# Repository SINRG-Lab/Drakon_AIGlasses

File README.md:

# Drakon AI Glasses

Hardware, firmware, 3D models, and the companion iOS app for Drakon AI smart glasses.

This repository is the single home for everything physical and embedded: board
designs, embedded firmware, printable frame parts, and the companion iOS app.
Measurement studies and backend services live in other repositories.

## Editions

The glasses come in two open-source editions that share a frame and audio
pipeline but differ in how they reach the network.

| Edition | Directory | Connectivity | Status |
|---|---|---|---|
| Companion | [`companion/`](companion/) | Wi-Fi / BLE, relayed via a paired device | v3 fabricated, v4 in design |
| Standalone | [`standalone/`](standalone/) | On-board cellular | v1 in design |

## Versions

Each edition is numbered independently — `companion/v3` and `standalone/v1` are
unrelated designs. Numbering continues each edition's own history, so the
companion boards start at v3 to match the `pcbv3` the team already builds.

| Version | Status |
|---|---|
| [`companion/v3`](companion/v3/) | **Current** — left and right boards fabricated |
| [`companion/v4`](companion/v4/) | Next — in design, empty |
| [`standalone/v1`](standalone/v1/) | First board — in design, empty |

A new version directory is created when the PCB changes in a way that breaks
compatibility with existing firmware or frame parts. Small fixes land in the
existing version. See [`docs/versioning.md`](docs/versioning.md).

## Layout

Every build is **two PCBs**, one per temple, so `hardware/` splits left/right.

```
<edition>/<version>/
├── firmware/            Embedded source for that board version
│   ├── src/  include/  lib/
├── hardware/
│   ├── left/            Left temple board
│   │   ├── kicad/       The KiCad project — .kicad_pro, .kicad_sch, .kicad_pcb
│   │   ├── fabrication/ gerbers/ and position/ files as sent to the fab
│   │   ├── bom/         Bills of materials
│   │   └── exports/     Schematic PDFs, STEP models, renders
│   ├── right/           Right temple board — same layout
│   └── shared/          Symbols, footprints and datasheets used by both
└── 3d-models/
    ├── cad/             Editable CAD source (STEP, SLDPRT, F3D)
    ├── exports/         Print-ready meshes (STL, 3MF)
    └── renders/         Images for docs and papers

common/                  Shared across editions and versions
├── firmware/  hardware/  3d-models/  scripts/

docs/
├── specs/  assembly/  bring-up/  versioning.md
```

The companion edition also contains the XIAO development firmware at
[`companion/firmware/S3_App_V2/`](companion/firmware/S3_App_V2/) and the iOS
app at [`companion/ios/`](companion/ios/). These came from the MK3.5 development
work; the firmware targets **XIAO ESP32-S3 Sense**, with its own pin map. It is
not a firmware release for the ESP32-C6 v3 boards. See the
[companion setup instructions](companion/README.md#software).

## Conventions

- **Keep each KiCad project in one directory.** `.kicad_pro`, `.kicad_sch` and
  `.kicad_pcb` must sit together under `kicad/` or the project will not open.
- **Put a file under `common/` only once a second edition or version actually
  uses it.** Premature sharing is harder to undo than duplication.
- **Commit CAD source alongside exports.** An STL with no editable source is a
  dead end.
- **Commit fabrication outputs even though they are generated.** They are the
  exact files sent to the fab; regenerating from a newer KiCad will not
  reproduce what was actually built.
- **Never commit secrets.** Firmware credentials belong in an ignored
  `config.h` beside a committed `config.h.template`.
- **Do not commit KiCad backups, `fp-info-cache`, or `.kicad_prl`.** They are
  local caches and editor state; `.gitignore` covers them.

## Git LFS

CAD, mesh, fabrication and datasheet binaries are tracked with
[Git LFS](https://git-lfs.com) — see [`.gitattributes`](.gitattributes). Run
this once per clone, before adding any such files:

```
git lfs install
```

Note that binaries committed before LFS was configured remain ordinary blobs in
history. Converting them requires `git lfs migrate`, which rewrites history and
needs a force-push — coordinate with the team before doing it.

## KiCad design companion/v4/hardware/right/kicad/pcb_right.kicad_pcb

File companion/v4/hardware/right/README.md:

# Companion v3 — Right Hinge Board

KiCad project `pcb_right`. Board outline **40.0 × 20.2 mm**, 16 components —
a smaller board than the left, with no battery.

| Directory | Contents |
|---|---|
| `kicad/` | `pcb_right.kicad_pro`, `.kicad_sch`, `.kicad_pcb`, library tables |
| `fabrication/position/` | `CPL_V4_RIGHT.csv`, `pcb_right-top.CSV` |
| `bom/` | `BOM_V4_RIGHT.csv`, `pcb_right.csv` |
| `exports/` | `pcb_right.step` |

Symbols and footprints are in [`../shared/symbols/`](../shared/symbols/),
shared with the left board.

## ⚠ No gerbers exist for this board

The original upload had a folder called `pcbv3_right_frabrication_files`, but
its `gerber/` subfolder did **not** contain this board. Those files were a
second export of the *left* board, and have been moved to
[`../left/fabrication/gerbers-2026-06-04/`](../left/fabrication/gerbers-2026-06-04/).

Three independent checks agree:

| Check | Left board | Right board | The misfiled gerbers |
|---|---|---|---|
| Edge cuts outline | 58.64 × 12.9 mm | 40.0 × 20.2 mm | 58.64 × 12.9 mm |
| Drill-pattern match | — | 2.1% | 70.8% to the left board |
| `%TF.ProjectId` | `pcbvr_left` | — | `pcbvr_left` |

**Anyone who sent that folder to a fab would have received a second left
board.** Export gerbers from `kicad/pcb_right.kicad_pcb` before ordering.

The BOM and position files in this directory *are* genuinely this board — their
designators (`C1`–`C4`, `FB1`, `FB2`, `J1`, `J2`, `R1`–`R3`, `SW1`, `U1`, `U2`)
all fall within its 16 components and include none of the left board's
battery, diodes or extra passives. Only the gerbers were misfiled.

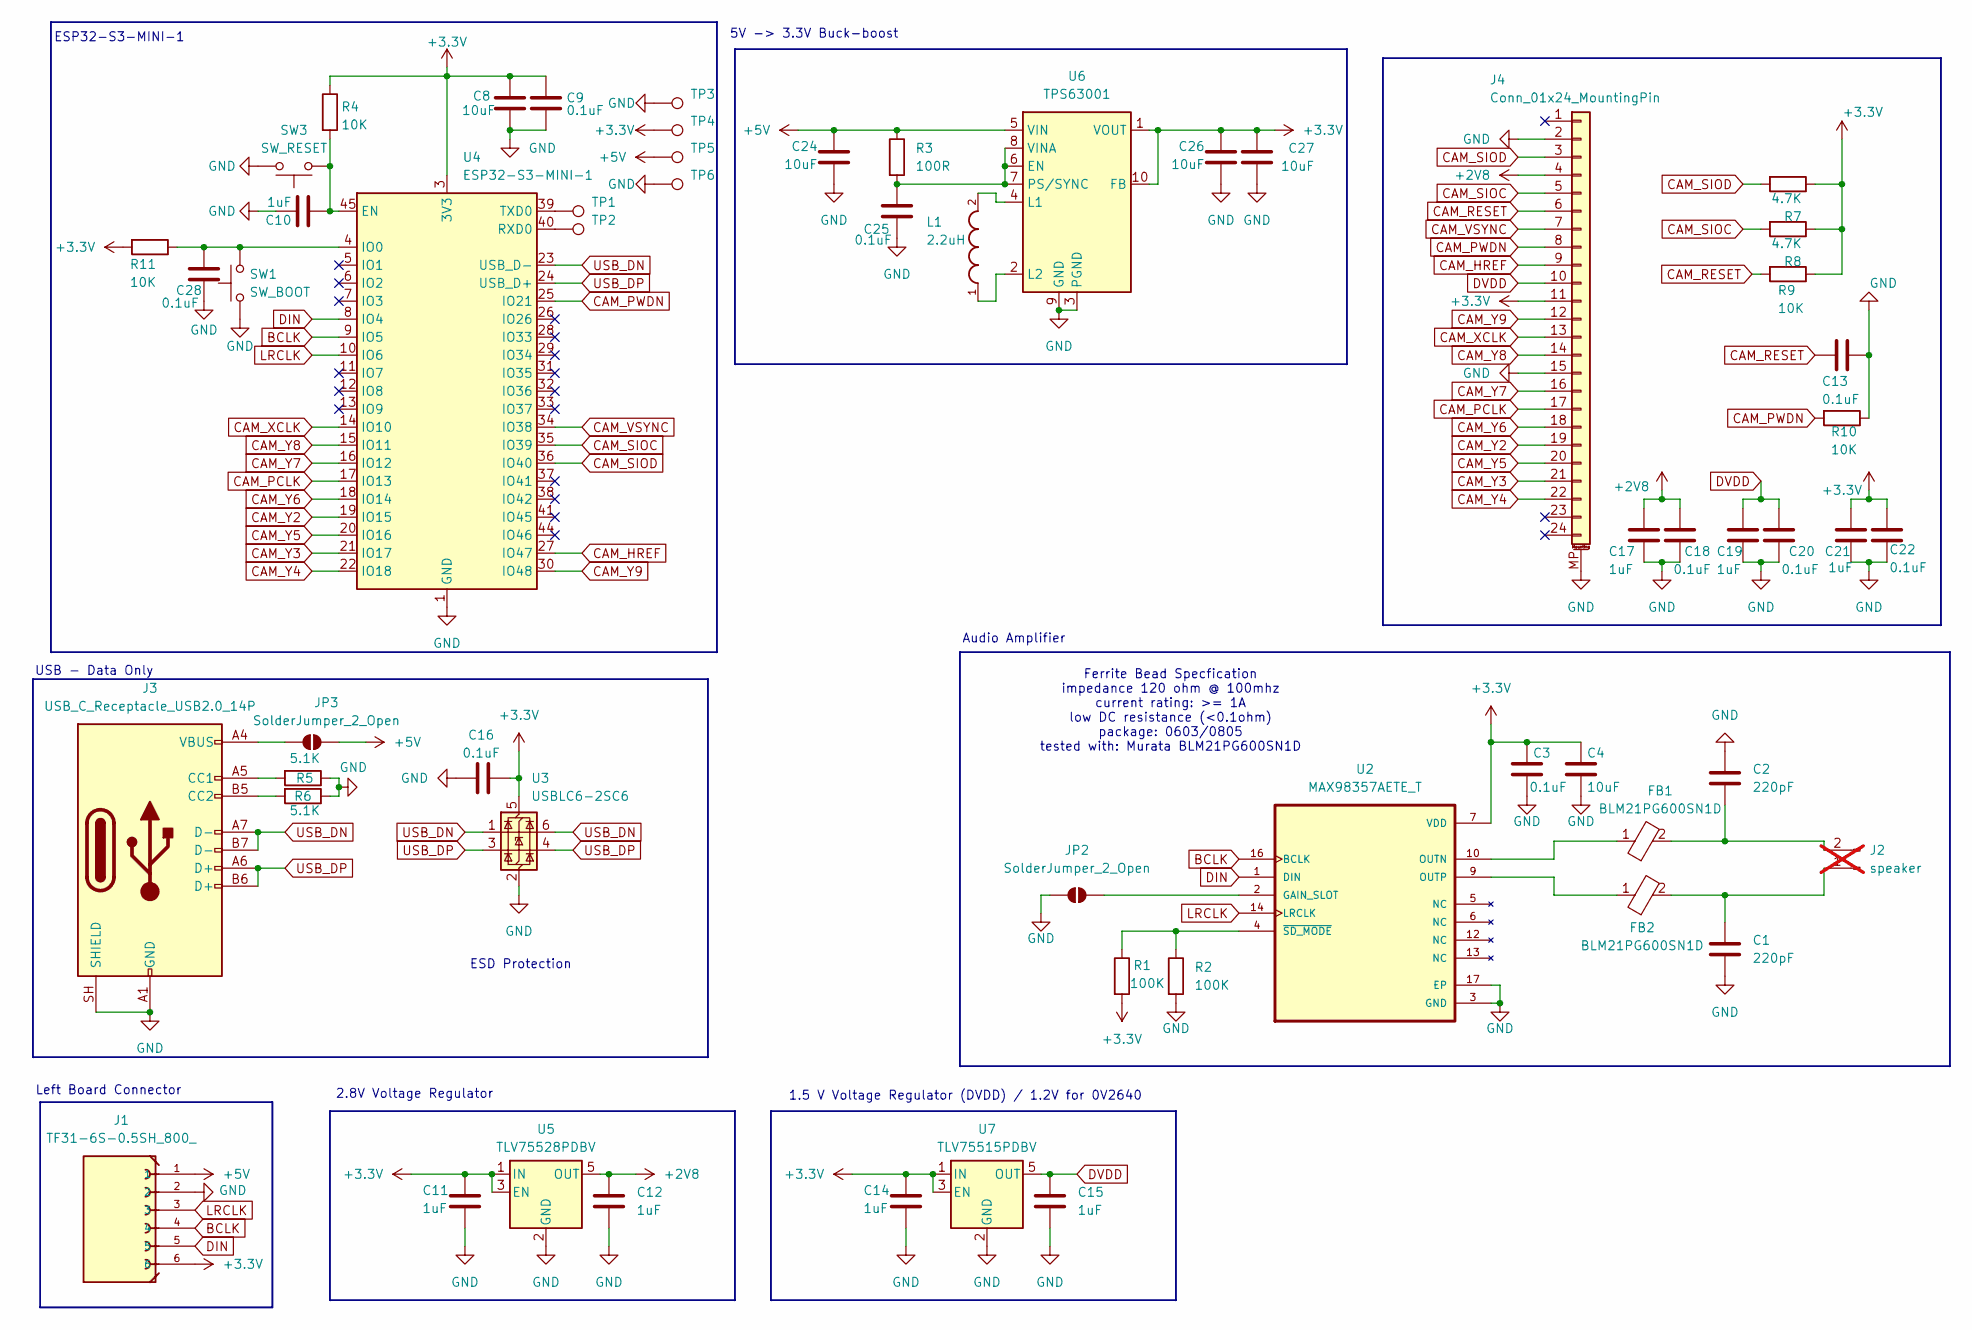
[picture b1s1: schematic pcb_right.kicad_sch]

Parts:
C1, C2: 220pF; C_0805_2012Metric_Pad1.18x1.45mm_HandSolder; Manufacturer_Part_Number CC0805KRX7R9BB221; JLCPCB_Part# C107145
C3: 0.1uF; C_0805_2012Metric_Pad1.18x1.45mm_HandSolder; Manufacturer_Part_Number CC0805KRX7R9BB104; JLCPCB_Part# C49678
C4: 10uF; C_0805_2012Metric_Pad1.18x1.45mm_HandSolder; Manufacturer_Part_Number CL21A106KAYNNNE; JLCPCB_Part# C15850
C8, C24, C26, C27: 10uF; C_0402_1005Metric; Manufacturer_Part_Number CL05A106MP5NUNC; JLCPCB_Part# C315248
C9, C13, C16, C18, C20, C22, C25, C28: 0.1uF; C_0402_1005Metric; Manufacturer_Part_Number CL05B104KO5NNNC; JLCPCB_Part# C1525
C10, C11, C12, C14, C15, C17, C19, C21: 1uF; C_0402_1005Metric; Manufacturer_Part_Number CL05A105KA5NQNC; JLCPCB_Part# C52923
FB1, FB2: BLM21PG600SN1D; BLM21AG102BH1J; Mouser Part Number 81-BLM21P600S
J1: TF31-6S-0.5SH_800_; HRS_TF31-6S-0.5SH_800_; Manufacturer_Part_Number TF31-6S-0.5SH(800); JLCPCB_Part# C3195341
J2: speaker; PinHeader_1x02_P2.54mm_Vertical; not fitted
J3: USB_C_Receptacle_USB2.0_14P; USB_C_Receptacle_HRO_TYPE-C-31-M-12; Manufacturer_Part_Number TYPE-C-31-M-12; JLCPCB_Part# C165948
J4: Conn_01x24_MountingPin; Hirose_FH12-24S-0.5SH_1x24-1MP_P0.50mm_Horizontal; Manufacturer_Part_Number FH12-24S-0.5SH(55); JLCPCB_Part# C202112
JP2, JP3: SolderJumper_2_Open; SolderJumper-2_P1.3mm_Open_RoundedPad1.0x1.5mm
L1: 2.2uH; INDC2520X120N; Manufacturer_Part_Number DFE252012F-2R2M=P2; JLCPCB_Part# C576403
R1, R2: 100K; R_0805_2012Metric_Pad1.20x1.40mm_HandSolder; Manufacturer_Part_Number 0805W8F1003T5E; JLCPCB_Part# C149504
R3: 100R; R_0805_2012Metric_Pad1.20x1.40mm_HandSolder; Manufacturer_Part_Number 0805W8F1000T5E; JLCPCB_Part# C17408
R4, R11: 10K; R_0402_1005Metric; Manufacturer_Part_Number 0402WGF1002TCE; JLCPCB_Part# C25744
R5, R6: 5.1K; R_0402_1005Metric; Manufacturer_Part_Number 0402WGF5101TCE; JLCPCB_Part# C25905
R7, R8: 4.7K; R_0805_2012Metric_Pad1.20x1.40mm_HandSolder; Manufacturer_Part_Number 0805W8F4701T5E; JLCPCB_Part# C17673
R9, R10: 10K; R_0805_2012Metric_Pad1.20x1.40mm_HandSolder; Manufacturer_Part_Number 0805W8F1002T5E; JLCPCB_Part# C17414
SW1: SW_BOOT; SW_SPST_PTS810; Manufacturer_Part_Number PTS810SJG250SMTRLFS; JLCPCB_Part# C221895
SW3: SW_RESET; SW_SPST_PTS810; Manufacturer_Part_Number PTS810SJG250SMTRLFS; JLCPCB_Part# C221895
TP1: TX; TestPoint_Pad_D1.5mm
TP2: RX; TestPoint_Pad_D1.5mm
TP3, TP4, TP5, TP6: GND; TestPoint_Pad_D1.5mm
U2: MAX98357AETE_T; QFN50P300X300X80-17N; Manufacturer_Part_Number MAX98357AETE+T; JLCPCB_Part# C910544
U3: USBLC6-2SC6; SOT-23-6; Manufacturer_Part_Number USBLC6-2SC6; JLCPCB_Part# C7519
U4: ESP32-S3-MINI-1; ESP32-S2-MINI-1; Manufacturer_Part_Number ESP32-S3-MINI-1-N4R2; JLCPCB_Part# C3013941
U5: TLV75528PDBV; SOT-23-5; Manufacturer_Part_Number TLV75528PDBVR; JLCPCB_Part# C2868951
U6: TPS63001; Texas_DRC0010J_ThermalVias; Manufacturer_Part_Number TPS63001DRCR; JLCPCB_Part# C28060
U7: TLV75515PDBV; SOT-23-5; Manufacturer_Part_Number TLV75515PDBVR; JLCPCB_Part# C2867152

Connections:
+2V8: C12.1, C17.1, C18.1, J4.4, U5.5 (OUT)
+3.3V: C3.1, C4.1, C8.1, C9.1, C11.1, C14.1, C16.2, C21.1, C22.1, C26.1, C27.1, J1.6, J4.11, R1.2, R4.1, R7.1, R8.1, R9.1, R11.2, TP4.1 (1_1), U2.7 (VDD), U2.8 (VDD), U3.5 (VBUS), U4.3 (3V3), U5.1 (IN), U5.3 (EN), U6.1 (VOUT), U6.10 (FB), U7.1 (IN), U7.3 (EN)
+5V: C24.1, J1.1, JP3.2 (B), R3.1, TP5.1 (1_1), U6.5 (VIN)
BCLK: J1.4, U2.16 (BCLK), U4.9 (IO5)
CAM_HREF: J4.9, U4.27 (IO47)
CAM_PCLK: J4.17, U4.17 (IO13)
CAM_PWDN: J4.8, R10.2, U4.25 (IO21)
CAM_RESET: C13.2, J4.6, R9.2
CAM_SIOC: J4.5, R8.2, U4.35 (IO39)
CAM_SIOD: J4.3, R7.2, U4.36 (IO40)
CAM_VSYNC: J4.7, U4.34 (IO38)
CAM_XCLK: J4.13, U4.14 (IO10)
CAM_Y2: J4.19, U4.19 (IO15)
CAM_Y3: J4.21, U4.21 (IO17)
CAM_Y4: J4.22, U4.22 (IO18)
CAM_Y5: J4.20, U4.20 (IO16)
CAM_Y6: J4.18, U4.18 (IO14)
CAM_Y7: J4.16, U4.16 (IO12)
CAM_Y8: J4.14, U4.15 (IO11)
CAM_Y9: J4.12, U4.30 (IO48)
DIN: J1.5, U2.1 (DIN), U4.8 (IO4)
DVDD: C15.1, C19.1, C20.1, J4.10, U7.5 (OUT)
GND: C1.2, C2.1, C3.2, C4.2, C8.2, C9.2, C10.2, C11.2, C12.2, C13.1, C14.2, C15.2, C16.1, C17.2, C18.2, C19.2, C20.2, C21.2, C22.2, C24.2, C25.2, C26.2, C27.2, C28.2, J1.2, J3.A1 (GND), J3.A12 (GND), J3.B1 (GND), J3.B12 (GND), J3.SH (SHIELD), J4.2, J4.15, J4.MP (MountPin), JP2.1 (A), R2.2, R5.1, R6.1, R10.1, SW1.1, SW3.2, TP3.1 (1_1), TP6.1 (1_1), U2.3 (GND), U2.11 (GND), U2.15 (GND), U2.17 (EP), U3.2 (GND), U4.1 (GND), U4.2 (GND), U4.42 (GND), U4.43 (GND), U4.46 (GND), U4.47 (GND), U4.48 (GND), U4.49 (GND), U4.50 (GND), U4.51 (GND), U4.52 (GND), U4.53 (GND), U4.54 (GND), U4.55 (GND), U4.56 (GND), U4.57 (GND), U4.58 (GND), U4.59 (GND), U4.60 (GND), U4.61 (GND), U4.62 (GND), U4.63 (GND), U4.64 (GND), U4.65 (GND), U5.2 (GND), U6.3 (PGND), U6.9 (GND), U6.11 (PGND), U7.2 (GND)
LRCLK: J1.3, U2.14 (LRCLK), U4.10 (IO6)
unnamed: C1.1, FB2.2, J2.1
unnamed: C2.2, FB1.2, J2.2
unnamed: J3.A5 (CC1), R5.2
unnamed: J3.B5 (CC2), R6.2
unnamed: JP2.2 (B), U2.2 (GAIN_SLOT)
unnamed: J3.A4 (VBUS), J3.A9 (VBUS), J3.B4 (VBUS), J3.B9 (VBUS), JP3.1 (A)
unnamed: FB1.1, U2.10 (OUTN)
unnamed: FB2.1, U2.9 (OUTP)
unnamed: R1.1, R2.1, U2.4 (~SD_MODE)
unnamed: C10.1, R4.2, SW3.1, U4.45 (EN)
unnamed: C28.1, R11.1, SW1.2, U4.4 (IO0)
unnamed: TP2.1 (1_1), U4.40 (RXD0)
unnamed: TP1.1 (1_1), U4.39 (TXD0)
unnamed: C25.1, R3.2, U6.6 (EN), U6.7 (PS/SYNC), U6.8 (VINA)
unnamed: L1.2, U6.4 (L1)
unnamed: L1.1, U6.2 (L2)
USB_DN: J3.A7 (D-), J3.B7 (D-), U3.1 (I/O1), U3.6 (I/O1), U4.23 (USB_D-)
USB_DP: J3.A6 (D+), J3.B6 (D+), U3.3 (I/O2), U3.4 (I/O2), U4.24 (USB_D+)

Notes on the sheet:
1.5 V Voltage Regulator (DVDD) / 1.2V for 0V2640
USB - Data Only
ESP32-S3-MINI-1
Left Board Connector
Audio Amplifier
2.8V Voltage Regulator
5V -> 3.3V Buck-boost
ESD Protection
Ferrite Bead Specfication impedance 120 ohm @ 100mhz current rating: >= 1A low DC resistance (<0.1ohm) package: 0603/0805 tested with: Murata BLM21PG600SN1D

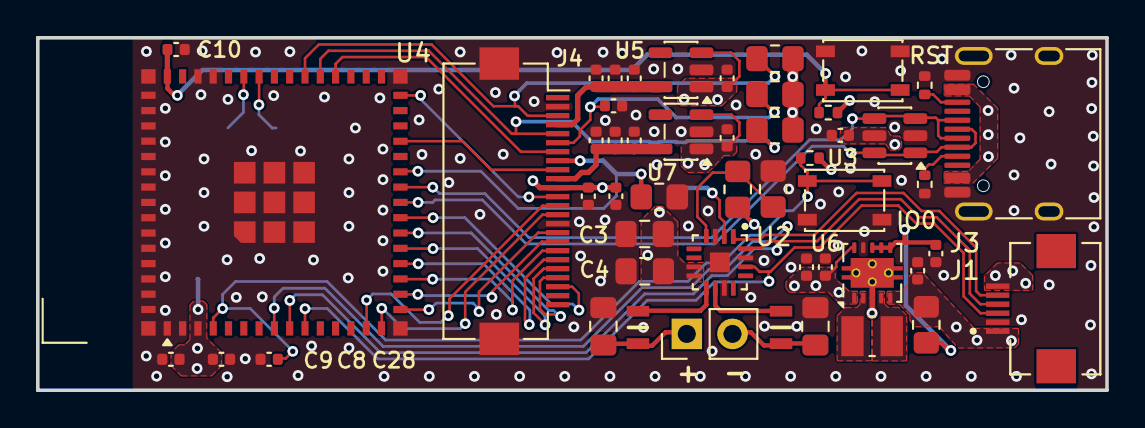
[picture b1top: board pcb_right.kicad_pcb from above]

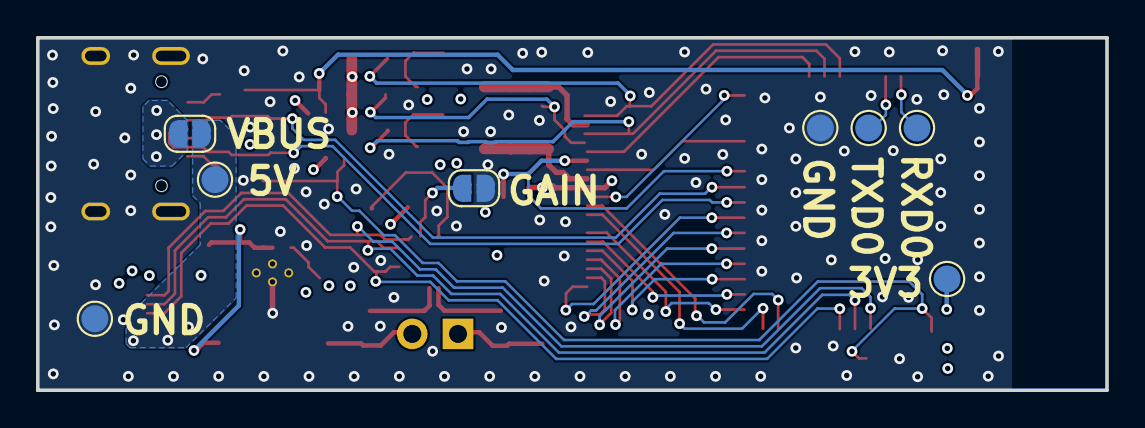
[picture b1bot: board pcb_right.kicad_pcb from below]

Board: 4 copper layers, 59.4 x 19.6 mm, 58 parts (8 on the bottom side), 42 nets.

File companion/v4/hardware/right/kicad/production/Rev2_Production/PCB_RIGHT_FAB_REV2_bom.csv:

Designator,Footprint,Quantity,Value,LCSC Part #
"C1, C2",805,2,220pF,C107145
"C10, C11, C12, C14, C15, C17, C19, C21",402,8,1uF,C52923
"C13, C16, C18, C20, C22, C25, C28, C9",402,8,0.1uF,C1525
"C24, C26, C27, C8",402,4,10uF,C315248
C3,805,1,0.1uF,C49678
C4,805,1,10uF,C15850
"FB1, FB2",BLM21AG102BH1J,2,BLM21PG600SN1D,C18305
J1,HRS_TF31-6S-0.5SH_800_,1,TF31-6S-0.5SH_800_,C3195341
J3,USB_C_Receptacle_HRO_TYPE-C-31-M-12,1,USB_C_Receptacle_USB2.0_14P,C165948
J4,Hirose_FH12-24S-0.5SH_1x24-1MP_P0.50mm_Horizontal,1,Conn_01x24_MountingPin,C202112
L1,INDC2520X120N,1,2.2uH,C576403
"R1, R2",805,2,100K,C149504
"R10, R9",805,2,10K,C17414
"R11, R4",402,2,10K,C25744
R3,805,1,100R,C17408
"R5, R6",402,2,5.1K,C25905
"R7, R8",805,2,4.7K,C17673
"SW1, SW3",SW_SPST_PTS810,2,SW,C221895
U2,QFN50P300X300X80-17N,1,MAX98357AETE_T,C910544
U3,SOT-23-6,1,USBLC6-2SC6,C7519
U4,ESP32-S2-MINI-1,1,ESP32-S3-MINI-1,C3013941
U5,SOT-23-5,1,TLV75528PDBV,C2868951
U6,Texas_DRC0010J_ThermalVias,1,TPS63001,C28060
U7,SOT-23-5,1,TLV75515PDBV,C2867152

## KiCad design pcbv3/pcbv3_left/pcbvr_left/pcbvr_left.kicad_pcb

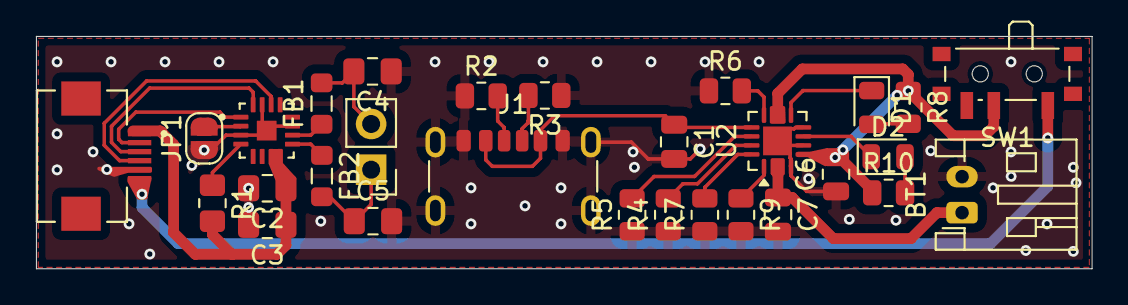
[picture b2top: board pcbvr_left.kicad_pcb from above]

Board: 2 copper layers, 58.6 x 12.9 mm, 29 parts (0 on the bottom side), 26 nets.

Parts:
BT1: Battery; JST_PH_S2B-PH-K_1x02_P2.00mm_Horizontal
C1: 1UF; C_0805_2012Metric
C2: 0.1UF; C_0805_2012Metric_Pad1.18x1.45mm_HandSolder
C3: 10UF; C_0805_2012Metric_Pad1.18x1.45mm_HandSolder
C4, C5: 220PF; C_0805_2012Metric_Pad1.18x1.45mm_HandSolder
C6, C7: 4.7uf; C_0805_2012Metric
D1: LED_R; LED_0805_2012Metric
D2: LED_G; LED_0805_2012Metric
FB1, FB2: FerriteBead; L_0805_2012Metric_Pad1.05x1.20mm_HandSolder
J1: USB_C_Receptacle_PowerOnly_6P; USB_C_Receptacle_GCT_USB4125-xx-x_6P_TopMnt_Horizontal
J2: speaker; PinHeader_1x02_P2.54mm_Vertical
J3: TF31-6S-0.5SH_800_; HRS_TF31-6S-0.5SH_800_
JP1: SolderJumper_2_Open; SolderJumper-2_P1.3mm_Open_RoundedPad1.0x1.5mm
R1: 100k; R_0805_2012Metric_Pad1.20x1.40mm_HandSolder
R2, R3: 5.1K; R_0805_2012Metric
R4: 4k; R_0805_2012Metric
R5: 46.4k; R_0805_2012Metric
R6, R7: 1k; R_0805_2012Metric
R8, R10: 1.5K; R_0805_2012Metric
R9: 10k; R_0805_2012Metric
SW1: SW_SPDT; SW_SPDT_PCM12
U1: MAX98357AETE_T; QFN50P300X300X80-17N
U2: BQ24074RGT; VQFN-16-1EP_3x3mm_P0.5mm_EP1.6x1.6mm

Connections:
+3.3V: C2.1, C3.1, J3.1, R1.2, U1.7 (VDD), U1.8 (VDD)
+5V: J3.6, SW1.1 (A)
BCLK: J3.3, U1.16 (BCLK)
DIN: J3.2, U1.1 (DIN)
GND: BT1.2 (-), C1.2, C2.2, C3.2, C4.1, C5.2, C6.1, C7.2, J1.A12 (GND), J1.B12 (GND), J1.S1 (SHIELD), J3.5, JP1.1 (A), R2.1, R3.1, R4.1, R5.1, R6.1, R7.1, R9.2, U1.3 (GND), U1.11 (GND), U1.15 (GND), U1.17 (EP), U2.4 (~CE), U2.6 (EN1), U2.8 (VSS), U2.17 (VSS)
LRCLK: J3.4, U1.14 (LRCLK)
unnamed: BT1.1 (+), C7.1, U2.2 (BAT), U2.3 (BAT)
unnamed: D1.2 (A), R8.2
unnamed: D1.1 (K), U2.9 (~CHG)
unnamed: D2.2 (A), R10.2
unnamed: D2.1 (K), U2.7 (~PGOOD)
unnamed: J1.A5 (CC1), R2.2
unnamed: J1.B5 (CC2), R3.2
unnamed: C5.1, FB2.2, J2.1
unnamed: C4.2, FB1.2, J2.2
unnamed: JP1.2 (B), U1.2 (GAIN_SLOT)
unnamed: FB1.1, U1.10 (OUTN)
unnamed: FB2.1, U1.9 (OUTP)
unnamed: R1.1, U1.4 (SD_MODE)
unnamed: R6.2, U2.12 (ILIM)
unnamed: C1.1, J1.A9 (VBUS), J1.B9 (VBUS), U2.13 (IN)
unnamed: R7.2, U2.16 (ISET)
unnamed: R4.2, U2.15 (ITERM)
unnamed: R5.2, U2.14 (TMR)
unnamed: R9.1, U2.1 (TS)
out: C6.2, R8.1, R10.1, SW1.2 (B), U2.5 (EN2), U2.10 (OUT), U2.11 (OUT)

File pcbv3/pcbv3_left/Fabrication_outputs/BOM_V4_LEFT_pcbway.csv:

"PCBWay Bom Quotation, Product No.:T-X6W1030650A",,,,,,,,,,,,,,
Item #,*Designator,*Qty,Manufacturer,*Mfg Part #,Description / Value,Vendor Part #,*Package/Footprint,*Unit Price(5 units),*Total,*Delivery Time,*Actual Purchase Mfg Part #,*PCBWay Note,Customer Reply,PCBWay Update
1,J3,1,Hirose Electric Co Ltd,TF31-6S-0.5SH(800),"TF31-6S-0.5SH_800_『 』6 Position FFC, FPC Connector Contacts, Bottom 0.020 (0.50mm) Surface Mount, Right Angle",26-TF31-6S-0.5SH(800)CT-ND,HRS_TF31-6S-0.5SH_800_,$0.395,$1.975,,,,,
2,D2,1,Lite-On Inc.,LTST-C171KGKT,LED_G『 』Green 571nm LED Indication - Discrete 2V 0805 (2012 Metric),160-1426-1-ND,LED_0805_2012Metric,$0.036,$0.180,,,,,
3,R1,1,Panasonic Industry,ERA-6AEB104V,"100k『 』100 kOhms ±0.1% 0.125W, 1/8W Chip Resistor 0805 (2012 Metric) Automotive AEC-Q200 Thin Film",P100KDACT-ND,R_0805_2012Metric_Pad1.20x1.40mm_HandSolder,$0.473,$2.365,,,,,
4,"R3,R2",2,Panasonic Industry,ERJ-6GEYJ512V,"5.1K『 』5.1 kOhms ±5% 0.125W, 1/8W Chip Resistor 0805 (2012 Metric) Automotive AEC-Q200 Thick Film",P5.1KACT-ND,R_0805_2012Metric,$0.069,$0.690,,,,,
5,R5,1,Panasonic Industry,ERA-6AEB4642V,"46.4k『 』46.4 kOhms ±0.1% 0.125W, 1/8W Chip Resistor 0805 (2012 Metric) Automotive AEC-Q200 Thin Film",P46.4KDACT-ND,R_0805_2012Metric,$0.473,$2.365,,,,,
6,"C5,C4",2,Samsung Electro-Mechanics,CL21C221JBANNNC,"220PF『 』220 pF ±5% 50V Ceramic Capacitor C0G, NP0 0805 (2012 Metric)",1276-1164-1-ND,C_0805_2012Metric_Pad1.18x1.45mm_HandSolder,$0.076,$0.760,,,,,
7,"FB2,FB1",2,Murata Electronics,BLM21PG600SN1D,FerriteBead『 』60 Ohms @ 100 MHz 1 Power Line Ferrite Bead 0805 (2012 Metric) 3.5A 20mOhm,490-1053-1-ND,L_0805_2012Metric_Pad1.05x1.20mm_HandSolder,$0.075,$0.750,,,,,
8,U2,1,Texas Instruments,BQ24074RGTT,BQ24074RGT『 』Charger IC Lithium Ion 16-VQFN (3x3),296-23798-1-ND,VQFN-16-1EP_3x3mm_P0.5mm_EP1.6x1.6mm,$2.276,$11.380,,,,,
9,C2,1,NextGen Components,CL21B104KBCNNNC,0.1UF『 』0.1 µF ±10% 50V Ceramic Capacitor X7R 0805 (2012 Metric),1276-1003-1-ND,C_0805_2012Metric_Pad1.18x1.45mm_HandSolder,$0.158,$0.790,,,,,
10,"R10,R8",2,Panasonic Industry,ERA-6AEB152V,"1.5K『 』1.5 kOhms ±0.1% 0.125W, 1/8W Chip Resistor 0805 (2012 Metric) Automotive AEC-Q200 Thin Film",P1.5KDACT-ND,R_0805_2012Metric,$0.284,$2.840,,,,,
11,J1,1,GCT,USB4125-GF-A,"USB_C_Receptacle_PowerOnly_6P『 』USB-C (USB TYPE-C) Receptacle Connector 24 (6+18 Dummy) - Power Only 6 Pin Position Surface Mount, Right Angle; Through Hole",2073-USB4125-GF-ACT-ND,USB_C_Receptacle_GCT_USB4125-xx-x_6P_TopMnt_Horizontal,$1.159,$5.795,,,,,
12,U1,1,Analog Devices Inc./Maxim Integrated,MAX98357AETE+T,MAX98357AETE_T『 』Amplifier IC 1-Channel (Mono) Class D 16-TQFN (3x3),MAX98357AETE+TCT-ND,QFN50P300X300X80-17N,$1.181,$5.905,,,,,
13,SW1,1,C&K,PCM12SMTR,"SW_SPDT『 』Slide Switch SPDT Surface Mount, Right Angle",401-2016-1-ND,SW_SPDT_PCM12,$1.328,$6.640,,,,,
14,R7,1,Panasonic Industry,ERJ-6ENF1181V,"1.18k『 』1.18 kOhms ±1% 0.125W, 1/8W Chip Resistor 0805 (2012 Metric) Automotive AEC-Q200 Thick Film",P1.18KCCT-ND,R_0805_2012Metric,$0.116,$0.580,,,,,
15,"C7,C6",2,Samsung Electro-Mechanics,CL21A475KAQNNNE,4.7uf『 』4.7 µF ±10% 25V Ceramic Capacitor X5R 0805 (2012 Metric),1276-1244-1-ND,C_0805_2012Metric,$0.095,$0.950,,,,,
16,D1,1,Lite-On Inc.,160-1415-1-ND,LED_R『 』Red 631nm LED Indication - Discrete 2V 0805 (2012 Metric),160-1415-1-ND,LED_0805_2012Metric,$0.027,$0.135,,LTST-C170KRKT,,,
17,R6,1,Panasonic Industry,ERJ-6ENF1181V,"1.18k『 』1.18 kOhms ±1% 0.125W, 1/8W Chip Resistor 0805 (2012 Metric) Automotive AEC-Q200 Thick Film",P1.18KCCT-ND,R_0805_2012Metric,$0.116,$0.580,,,,,
18,R4,1,Panasonic Industry,ERJ-6GEYJ392V,"3.9 kOhms ±5% 0.125W, 1/8W Chip Resistor 0805 (2012 Metric) Automotive AEC-Q200 Thick Film",P3.9KACT-ND,R_0805_2012Metric,,,,,,,
19,R9,1,Panasonic Industry,ERJ-6ENF1002V,"10k『 』10 kOhms ±1% 0.125W, 1/8W Chip Resistor 0805 (2012 Metric) Automotive AEC-Q200 Thick Film",P10.0KCCT-ND,R_0805_2012Metric,$0.116,$0.580,,,,,
20,C3,1,Samsung Electro-Mechanics,CL21A106KOQNNNE,10UF『 』10 µF ±10% 16V Ceramic Capacitor X5R 0805 (2012 Metric),1276-1096-1-ND,C_0805_2012Metric_Pad1.18x1.45mm_HandSolder,$0.158,$0.790,,,,,
21,C1,1,Samsung Electro-Mechanics,CL21B104KBCNNNC,1UF『 』0.1 µF ±10% 50V Ceramic Capacitor X7R 0805 (2012 Metric),1276-1003-1-ND,C_0805_2012Metric,$0.158,$0.790,,,,,
,,,,,,,,Component Cost,$46.84,,,,,
